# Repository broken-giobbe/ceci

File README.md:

# ceci
Our IoT sensor/actuator nodes based around the ESP8266

## Folder "ceci-hardware"
Contains the PCB files, desgined in kicad. The files are stored in a subrepo
available here:
https://github.com/broken-giobbe/ceci-hardware

### Required Libraries:
**TODO**

## Folder "ceci-firmware"
Contains the firmware for the Arduino IDE.

### Required Libraries:
**TODO**

* [qd_sched](https://github.com/electricant/qd_sched) - simple scheduler for repetitive tasks
* To write data into ESP8266 SPIFFS the [Arduino ESP8266 filesystem uploader](https://github.com/esp8266/arduino-esp8266fs-plugin) plugin is required.

### Node configuration
After flashing the firmware rename data/config-example.ini to data/config.ini
and edit it to suit your flavour.

## Folder "octave-sim"
Contains the Octave simulation files to test the various heating algorithms.

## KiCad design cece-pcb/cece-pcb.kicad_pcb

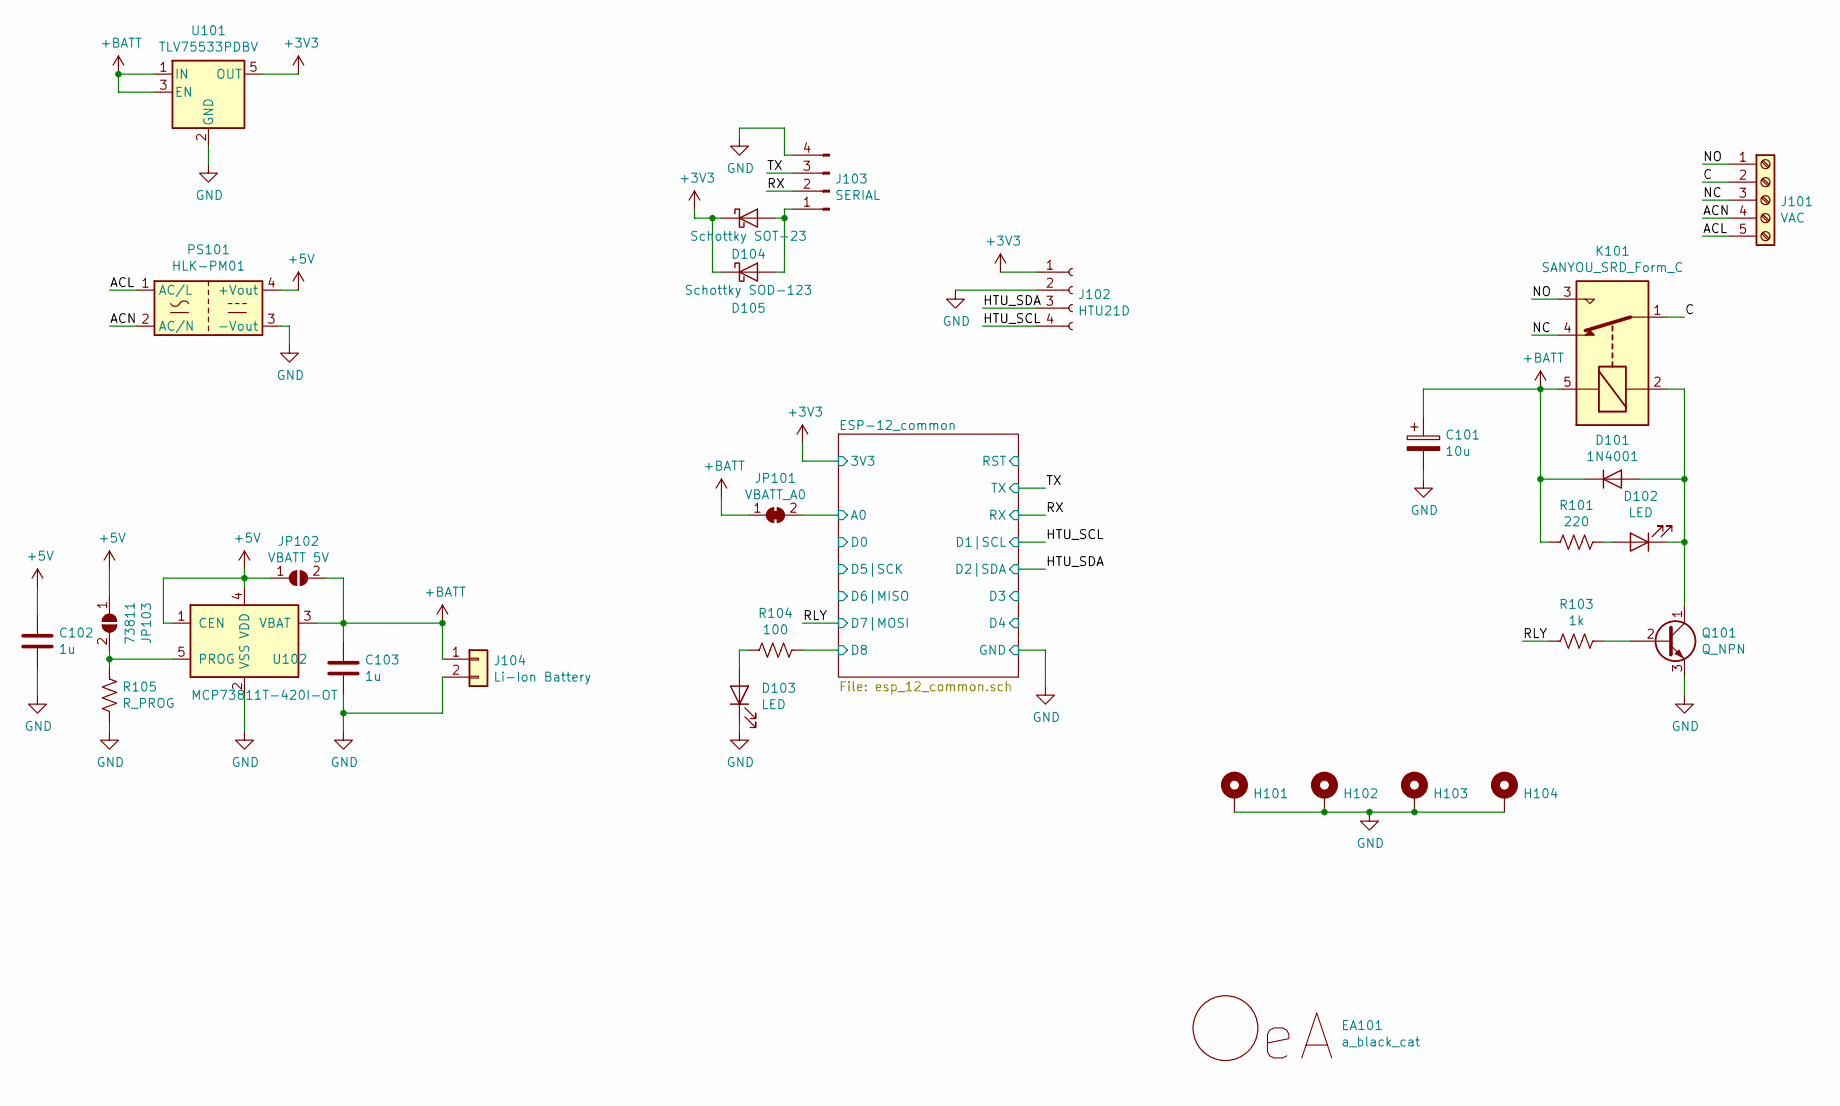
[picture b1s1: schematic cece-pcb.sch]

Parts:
C101: 10u; C_Radial_D6.3mm_H5.0mm_P2.50mm
C102, C103: 1u; C_Radial_D6.3mm_H5.0mm_P2.50mm
D101: 1N4001; D_DO-41_SOD81_P7.62mm_Horizontal
D102, D103: LED; LED_D3.0mm
D104: Schottky SOT-23; D_SOT-23_ANK
D105: Schottky SOD-123; D_SOD-123F
EA101: a_black_cat
H101, H102, H103, H104: MountingHole_Pad; MountingHole_3.2mm_M3_Pad
J101: VAC; TerminalBlock_bornier-5_P5.08mm
J102: HTU21D; PinHeader_1x04_P2.54mm_Vertical
J103: SERIAL; PinHeader_1x04_P2.54mm_Vertical
J104: Li-Ion Battery; PinHeader_1x02_P2.54mm_Vertical
JP101: VBATT_A0; SolderJumper-2_P1.3mm_Bridged_Pad1.0x1.5mm
JP102: VBATT 5V; SolderJumper-2_P1.3mm_Open_Pad1.0x1.5mm
JP103: 73811; SolderJumper-2_P1.3mm_Open_Pad1.0x1.5mm
K101: SANYOU_SRD_Form_C; Relay_SPDT_SANYOU_SRD_Series_Form_C
PS101: HLK-PM01; Converter_ACDC_HiLink_HLK-PMxx
Q101: Q_NPN; TO-92L_Inline_Wide
R101: 220; R_Axial_DIN0207_L6.3mm_D2.5mm_P7.62mm_Horizontal
R103: 1k; R_Axial_DIN0207_L6.3mm_D2.5mm_P7.62mm_Horizontal
R104: 100; R_Axial_DIN0207_L6.3mm_D2.5mm_P7.62mm_Horizontal
R105: R_PROG; R_0805_2012Metric_Pad1.15x1.40mm_HandSolder
U101: TLV75533PDBV; SOT-23-5
U102: MCP73811T-420I-OT; SOT-23-5

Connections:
+3V3: D104.1 (K), D105.1 (K), J102.1, U101.5 (OUT); also elsewhere on the board
+5V: C102.1, JP102.1 (A), JP103.1 (A), PS101.4 (+Vout), U102.1 (CEN), U102.4 (VDD)
+BATT: C101.1, C103.1, D101.1 (K), J104.1, JP101.1 (A), JP102.2 (B), K101.5, R101.2, U101.1 (IN), U101.3 (EN), U102.3 (VBAT)
/ACL: J101.5, PS101.1 (AC/L)
/ACN: J101.4, PS101.2 (AC/N)
/C: J101.2, K101.1
/ESP-12_common/A0: JP101.2 (B); also elsewhere on the board
/ESP-12_common/D8: R104.1; also elsewhere on the board
/HTU_SCL: J102.4; also elsewhere on the board
/HTU_SDA: J102.3; also elsewhere on the board
/NC: J101.3, K101.4
/NO: J101.1, K101.3
/RLY: R103.2; also elsewhere on the board
/RX: J103.2; also elsewhere on the board
/TX: J103.3; also elsewhere on the board
GND: C101.2, C102.2, C103.2, D103.1 (K), H101.1, H102.1, H103.1, H104.1, J102.2, J103.4, J104.2, PS101.3 (-Vout), Q101.3 (E), R105.2, U101.2 (GND), U102.2 (VSS); also elsewhere on the board
unnamed: D101.2 (A), D102.1 (K), K101.2, Q101.1 (C)
unnamed: D102.2 (A), R101.1
unnamed: D103.2 (A), R104.2
unnamed: D104.2 (A), D105.2 (A), J103.1
unnamed: JP103.2 (B), R105.1, U102.5 (PROG)
unnamed: Q101.2 (B), R103.1

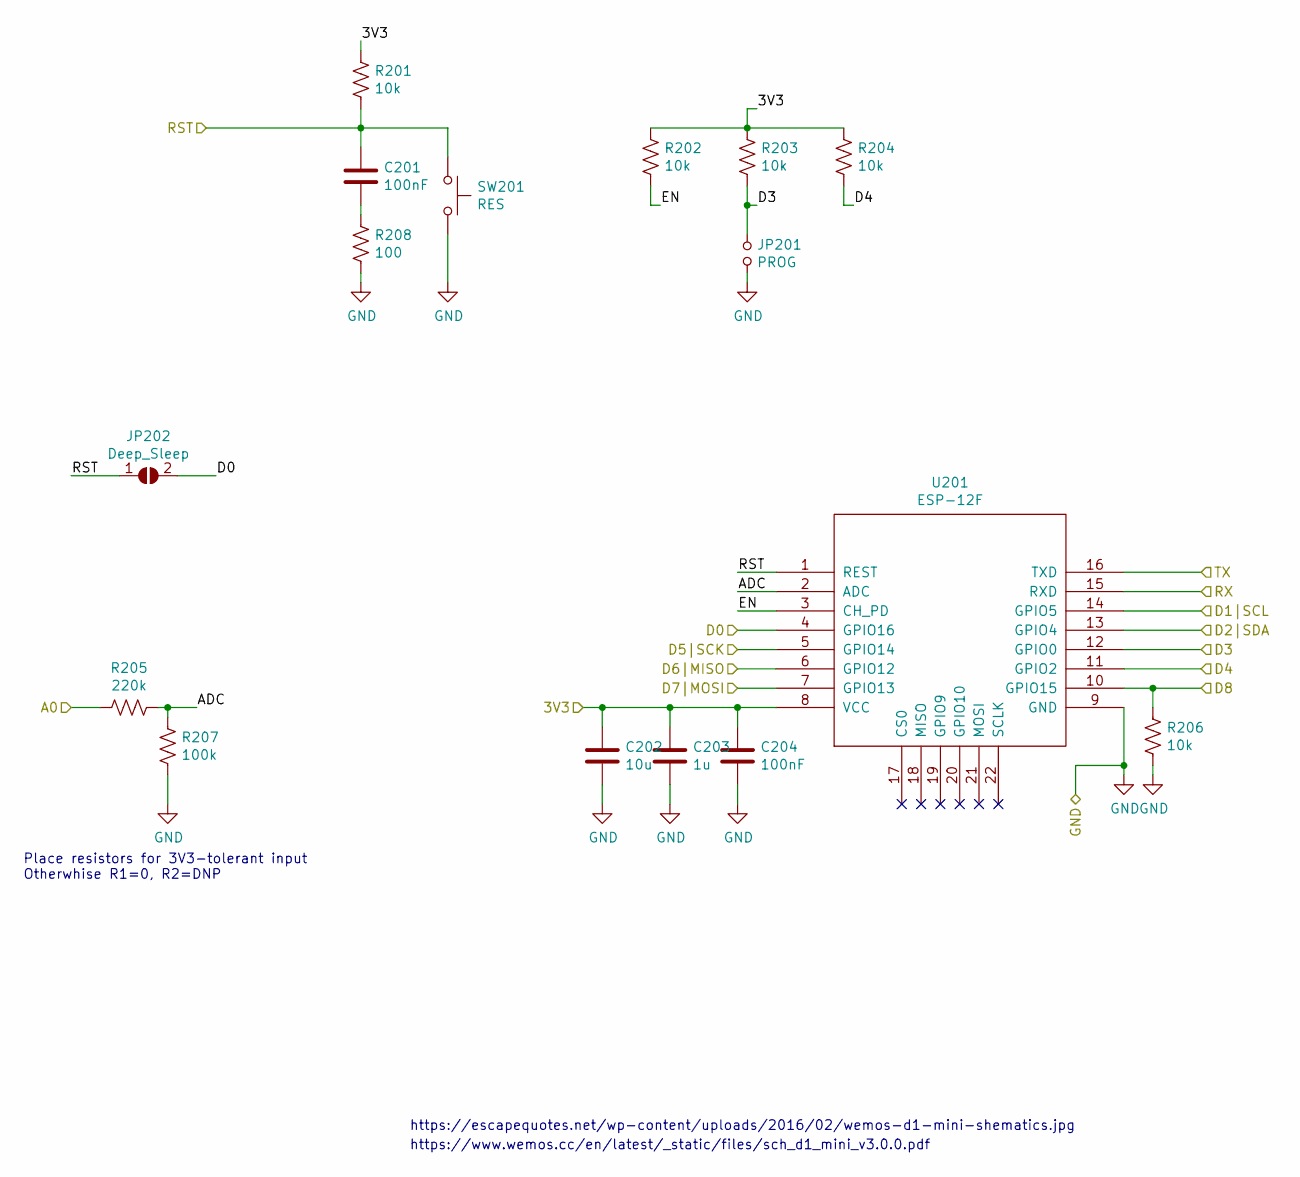
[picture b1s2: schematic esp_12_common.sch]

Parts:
C201, C204: 100nF; C_Disc_D4.3mm_W1.9mm_P5.00mm
C202: 10u; C_Radial_D6.3mm_H5.0mm_P2.50mm
C203: 1u; C_Radial_D6.3mm_H5.0mm_P2.50mm
JP201: PROG; PinHeader_1x02_P2.54mm_Vertical
JP202: Deep_Sleep; SolderJumper-2_P1.3mm_Open_Pad1.0x1.5mm
R201, R202, R203, R204, R206: 10k; R_Axial_DIN0207_L6.3mm_D2.5mm_P7.62mm_Horizontal
R205: 220k; R_Axial_DIN0207_L6.3mm_D2.5mm_P7.62mm_Horizontal
R207: 100k; R_Axial_DIN0207_L6.3mm_D2.5mm_P7.62mm_Horizontal
R208: 100; R_Axial_DIN0207_L6.3mm_D2.5mm_P7.62mm_Horizontal
SW201: RES; SW_PUSH_6mm
U201: ESP-12F; ESP-12E

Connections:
+3V3: C202.1, C203.1, C204.1, R201.1, R202.2, R203.2, R204.2, U201.8 (VCC); also elsewhere on the board
/ESP-12_common/A0: R205.2; also elsewhere on the board
/ESP-12_common/ADC: R205.1, R207.1, U201.2 (ADC)
/ESP-12_common/D0: JP202.2 (B), U201.4 (GPIO16)
/ESP-12_common/D3: JP201.1, R203.1, U201.12 (GPIO0)
/ESP-12_common/D4: R204.1, U201.11 (GPIO2)
/ESP-12_common/D5|SCK: U201.5 (GPIO14)
/ESP-12_common/D6|MISO: U201.6 (GPIO12)
/ESP-12_common/D8: R206.2, U201.10 (GPIO15); also elsewhere on the board
/ESP-12_common/EN: R202.1, U201.3 (CH_PD)
/ESP-12_common/RST: C201.1, JP202.1 (A), R201.2, SW201.1, U201.1 (REST)
/HTU_SCL: U201.14 (GPIO5); also elsewhere on the board
/HTU_SDA: U201.13 (GPIO4); also elsewhere on the board
/RLY: U201.7 (GPIO13); also elsewhere on the board
/RX: U201.15 (RXD); also elsewhere on the board
/TX: U201.16 (TXD); also elsewhere on the board
GND: C202.2, C203.2, C204.2, JP201.2, R206.1, R207.2, R208.2, SW201.2, U201.9 (GND); also elsewhere on the board
unnamed: C201.2, R208.1

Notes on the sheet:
Place resistors for 3V3-tolerant input Otherwhise R1=0, R2=DNP
https://escapequotes.net/wp-content/uploads/2016/02/wemos-d1-mini-shematics.jpg
https://www.wemos.cc/en/latest/_static/files/sch_d1_mini_v3.0.0.pdf

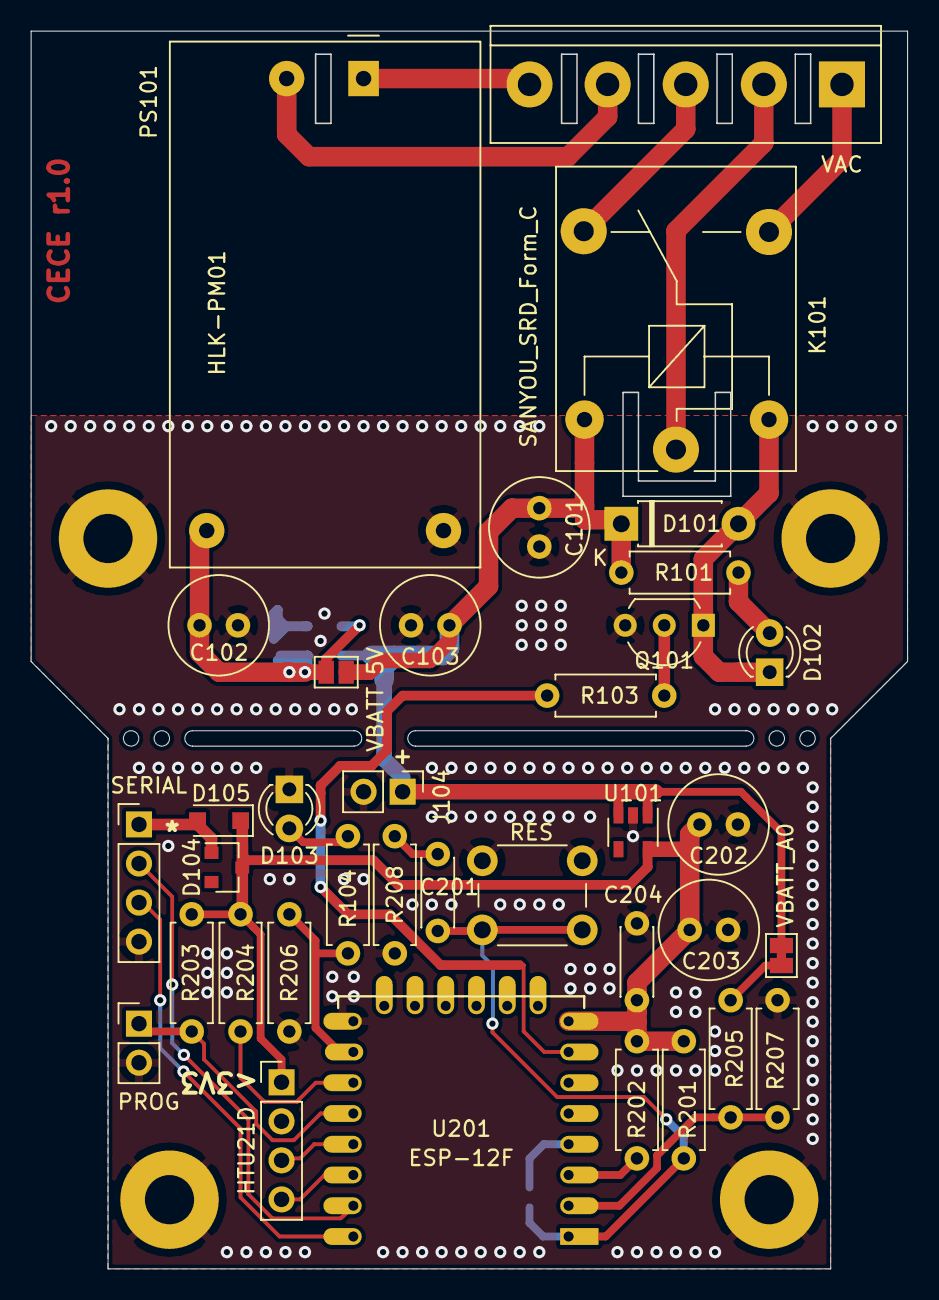
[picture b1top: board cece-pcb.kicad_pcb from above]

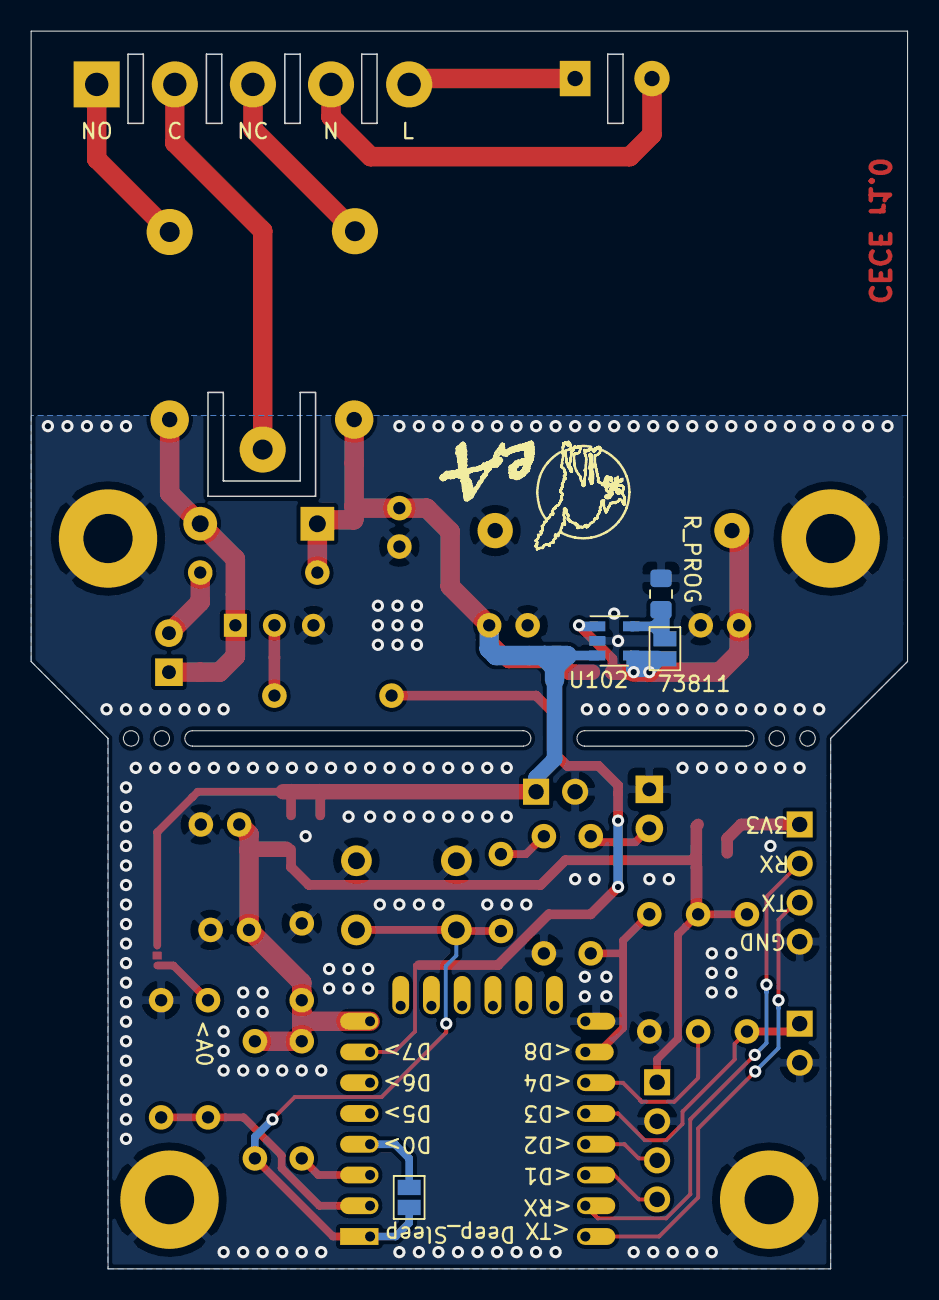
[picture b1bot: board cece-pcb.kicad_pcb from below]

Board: 2 copper layers, 57.0 x 80.5 mm, 45 parts (5 on the bottom side), 29 nets.

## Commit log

2020-11-29 Add firmware and PCB files
2020-12-01 Complete ESP-12 part of the PCB
2020-12-04 Finish first board revision
2020-12-04 Make board DRC-friendly
2020-12-04 Hang the ESP8266 antenna outside of the board for better RF performance
2020-12-04 More touches to the layout. Almost finished
2020-12-04 better grounding layout for regulator ICs
2020-12-05 Add jumper to send 5V directly to the LDO if no battery is installed
2020-12-05 Add rescue ifles
2020-12-05 Ignore more files
2020-12-05 Use SPIFFS to configure each sensor node.
2020-12-05 Better gitignore for config files
2020-12-06 Add gerber files
2020-12-30 Fix wrong footprint for the pin headers
2021-01-06 Create gerbers with the fixed pin header size
2021-02-03 Update component values
2021-02-03 Update schematic references to reflect hierarchy
2021-02-04 Boards have arrived. Fixed the many mistakes in the schematic
2021-02-04 Update PCB
2021-02-05 Use MQTT instead of HTTP
2021-02-08 Better gitignore for visual studio
2021-02-08 Better folder structure and lower power consumption during boot
2021-02-09 Reduce sensor resolution a bit for faster measurements
    The least significat digit is thrown out anyway
2021-02-09 Increase thermal relief size for easier hand soldering
2021-02-10 Update .gitignore to directory structure change
2021-02-10 Add temperature offset correction and update example config file
2021-02-10 Temperature offset is a float
2021-02-12 Add diode to protect the seral input when 3V3 are already supplied internally and shuffle stuff around a bit on the layout
2021-02-13 Add octave simulation files to test the heating algorithms
2021-02-13 Add initial stub code to support controlling the heating system
2021-02-15 Add stub code to act as a thermostat
2021-02-16 Fix MQTT handling logic for faster response times
2021-02-17 Add proper code to control the central heating
2021-02-22 Add resistor to limit peak current in the reset pushbutton. Prevents contact welding
2021-03-01 Fix hostname setting
2021-03-01 Add EA cat signature
2021-03-26 Use new stuff from pol lib
2021-04-04 Refactor the firmware a bit
2021-04-08 Move hardware design files into a submodule to allow for different HW revisions under the same firmware
2021-04-08 Follow the new naming conventions
2021-04-08 Use a scheduler to run the various tasks
2021-04-08 run mqtt.loop() more often and keep the relay on for at least a fixed amount of time
2021-07-06 Refactor the firmware to have the thermostat run independently from the MQTT tasks
2021-08-25 Deep code refactoring
    To allow for better hardware configurability the code has been deeply
    refactored. Now two different temperature sensors are supported and a UI
    driver is in the working.
    The final goal is having an header file to describe the current hardware
    implementation.
2021-08-25 Bump hardware revision to 1.02
2021-08-25 Use the node name as hostname instead of the default
2021-09-18 Implement the first version of a working GUI. More cleanups needed
2021-11-05 Add sysconfig.h file to configure the hardware globally
    The file also describes the future architecture of the firmware
2021-11-06 First round of refactoring to create mod_sensors
2021-11-07 Read MQTT config parameters from the global section of the ini file
2021-11-07 Build JSON string incrementally according to sensor capabilities
2021-11-07 Add MQTT dispatcher stub
2021-11-09 Move includes into the header file
2021-11-09 Add mod_thermostat stub (missing MQTT hooks)
2021-11-09 more refactoring to create mod_ui
2021-11-09 Fix typos
2021-11-10 Use less precision for the LM75 temperature sensor
2021-11-14 Get MQTT dispatcher ready to be used by the modules
2021-11-14 Make use of the MQTT callbacks
2021-11-14 Make the thermostat more accurate and the response time quicker
2021-11-17 Add support for BME680 ambient sensor
2021-11-19 Make MQTT sensor message more compact
2021-11-20 Update example config file to latest architectural changes
2021-11-26 Minor bugfixes + build for cece-fuori
2021-11-28 Log a message if measurement fails
2021-12-06 Fix wrong MQTT loop rate calculation from keepalive
2021-12-11 Add tasklet support for qd_sched + build for cece-caldaia
2021-12-11 Add mod_relay
2021-12-15 Enable different thermostat modes
2021-12-15 Log MQTT publish falure + build for cece-soggiorno
2022-01-07 USe tasklets for sendig thermostat status message
2022-01-09 Make BME680 measurements faster by not discarding readings to heat up the sensor
2022-02-23 Use running maximum to normalize air quality readings
2022-02-23 Increase anticipator cooldown rate
2022-02-23 Build for cece-fuori
2022-02-27 Make cooldown rate calculation faster
2022-02-27 Allow mod_ui to set thermostat state variables
2022-03-02 Reduce initial resistance value
2022-03-06 minor tweaks and bugfixes
2022-07-07 Add example octave file for ODE
2022-12-17 Implement tickless scheduler and various bugfixes
2022-12-27 Scheduler bugfixes for improved timing accuracy
2022-12-27 MQTT_KEEPALIVE is in seconds
2023-01-24 Create firmware version string from build date and remove unused variables
2023-01-24 Update hardware to latest revision
2023-02-06 Removed tasklets, they made the code needlessly complicated
2023-02-06 Move qdsched into an external library
2023-12-01 Support also platformio and enable different custom configs
2023-12-01 Fix build errors
2023-12-01 Ignore platformio files
2025-02-22 Implement birtwill message
2025-02-22 Use a slower-responding anticipator algorithm to avoid overshoot
2026-01-09 Add qd_Sched dependency and rework thermostat logic a bit
2026-01-09 Minor tweaks to mod_thermostat for better comments etc
2026-01-09 Add spreadsheet to run simulation of the effect of teh anticipator values
2026-01-09 Better rounding
